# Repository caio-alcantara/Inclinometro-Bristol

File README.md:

# Inclinometro-Bristol
Projeto de um inclinômetro desenvolvido para a Bristol. Um dispositivo capaz de medir a angulação de perfuratrizes e enviar esse dado via bluetooth para o operador da máquina.

Desenvolvedor: <a href="https://www.linkedin.com/in/caio-alcantara-santos/">Caio de Alcantara Santos</a>

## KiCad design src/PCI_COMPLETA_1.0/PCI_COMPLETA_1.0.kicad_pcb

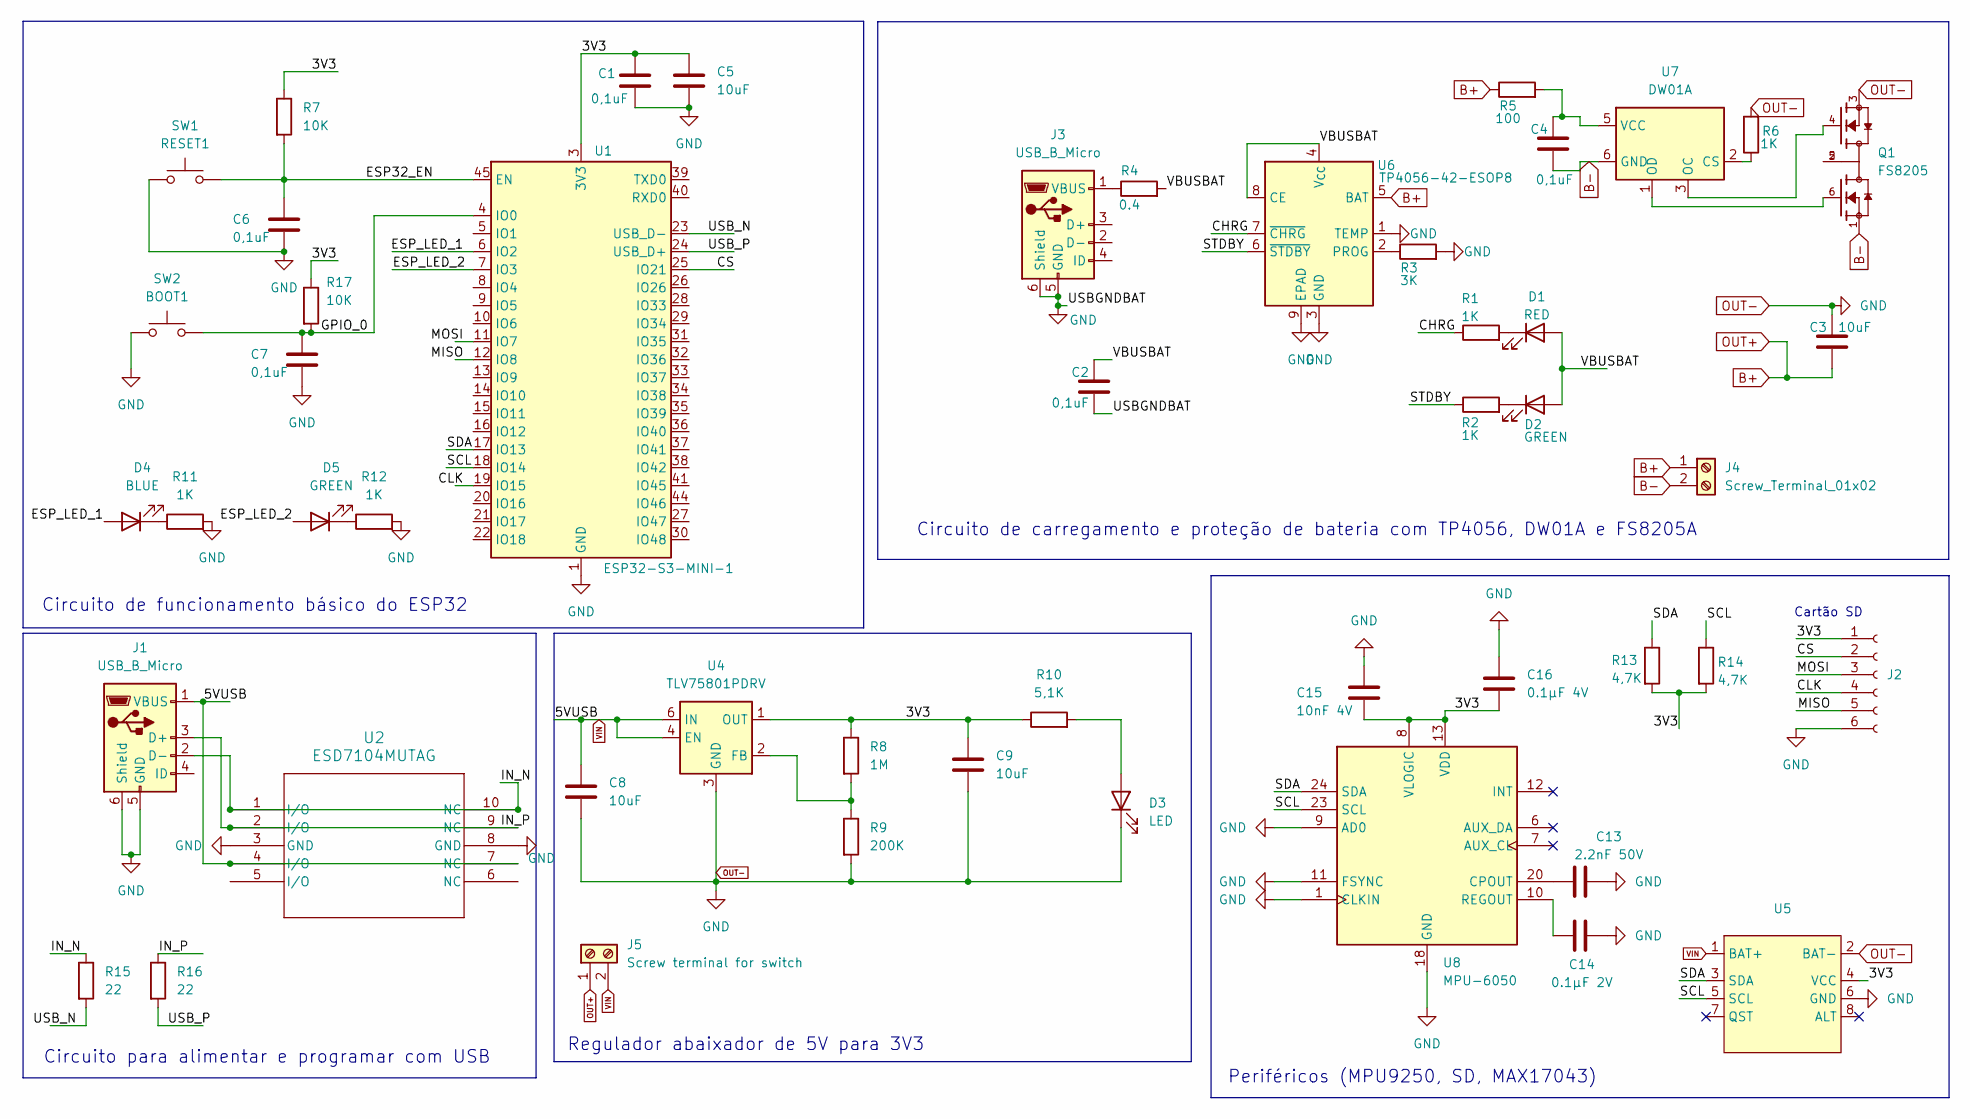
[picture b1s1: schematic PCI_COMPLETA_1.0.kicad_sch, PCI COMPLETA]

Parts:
C1, C2, C4, C6, C7: 0,1uF; C_0603_1608Metric
C3, C5, C8, C9: 10uF; C_0603_1608Metric
C13: 2.2nF 50V; C_0603_1608Metric
C14: 0.1µF 2V; C_0603_1608Metric
C15: 10nF 4V; C_0603_1608Metric
C16: 0.1µF 4V; C_0603_1608Metric
D1: RED; LED_0603_1608Metric
D2, D5: GREEN; LED_0603_1608Metric
D3: LED; LED_0603_1608Metric
D4: BLUE; LED_0603_1608Metric
J1, J3: USB_B_Micro; USB_Micro-B_Molex-105017-0001
J2: Conn_01x06_Socket; PinSocket_1x06_P2.54mm_Vertical
J4: Screw_Terminal_01x02; mors_2p
J5: Screw terminal for switch; mors_2p
Q1: FS8205; SOT95P280X145-6N; PARTREV 1.9
R1, R2, R6, R11, R12: 1K; R_0603_1608Metric
R3: 3K; R_0603_1608Metric
R4: 0.4; R_0603_1608Metric
R5: 100; R_0603_1608Metric
R7, R17: 10K; R_0603_1608Metric
R8: 1M; R_0603_1608Metric
R9: 200K; R_0603_1608Metric
R10: 5,1K; R_0603_1608Metric
R13, R14: 4,7K; R_0603_1608Metric
R15, R16: 22; R_0402_1005Metric
SW1: RESET1; SW_Push_1P1T_NO_CK_KSC6xxJ
SW2: BOOT1; SW_Push_1P1T_NO_CK_KSC6xxJ
U1: ESP32-S3-MINI-1; XCVR_ESP32-S3-MINI-1-N8
U2: ESD7104MUTAG; UDFN10_ONS
U4: TLV75801PDRV; WSON-6-1EP_2x2mm_P0.65mm_EP1x1.6mm
U5: MAX
U6: TP4056-42-ESOP8; SOIC-8-1EP_3.9x4.9mm_P1.27mm_EP2.41x3.3mm_ThermalVias
U7: DW01A; SOT-23-6
U8: MPU-6050; InvenSense_QFN-24_4x4mm_P0.5mm

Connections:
/3V3: C1.1, C5.1, C9.1, C15.2, C16.2, J2.1, R7.1, R8.1, R10.1, R13.2, R14.2, R17.1, U1.3 (3V3), U4.1 (OUT), U5.4 (VCC), U8.8 (VLOGIC), U8.13 (VDD)
/CHRG: R1.1, U6.7 (~CHRG)
/CLK: J2.4, U1.19 (IO15)
/CS: J2.2, U1.25 (IO21)
/ESP32_EN: C6.1, R7.2, SW1.2, U1.45 (EN)
/ESP_LED_1: D4.2 (A), U1.6 (IO2)
/ESP_LED_2: D5.2 (A), U1.7 (IO3)
/GPIO_0: C7.1, R17.2, SW2.2, U1.4 (IO0)
/IN_N: J1.2 (D-), R15.1, U2.1 (I/O), U2.10 (NC)
/IN_P: J1.3 (D+), R16.1, U2.2 (I/O), U2.9 (NC)
/MISO: J2.5, U1.12 (IO8)
/MOSI: J2.3, U1.11 (IO7)
/SCL: R14.1, U1.18 (IO14), U5.5 (SCL), U8.23 (SCL)
/SDA: R13.1, U1.17 (IO13), U5.3 (SDA), U8.24 (SDA)
/STDBY: R2.1, U6.6 (~STDBY)
/USB_N: R15.2, U1.23 (USB_D-)
/USB_P: R16.2, U1.24 (USB_D+)
/VBUSBAT: C2.1, D1.2 (A), D2.2 (A), R4.2, U6.4 (V_{CC}), U6.8 (CE)
B+: C3.2, J4.1, J5.1, R5.1, U6.5 (BAT)
B-: C4.2, J4.2, Q1.1, U7.6 (GND)
unnamed: D1.1 (K), R1.2
unnamed: D2.1 (K), R2.2
unnamed: D3.2 (A), R10.2
unnamed: D4.1 (K), R11.1
unnamed: D5.1 (K), R12.1
unnamed: J3.1 (VBUS), R4.1
unnamed: Q1.2, Q1.5
unnamed: R8.2, R9.1, U4.2 (FB)
unnamed: R3.1, U6.2 (PROG)
unnamed: R6.1, U7.2 (CS)
unnamed: Q1.4, U7.3 (OC)
unnamed: Q1.6, U7.1 (OD)
unnamed: C4.1, R5.2, U7.5 (VCC)
unnamed: C13.2, U8.20 (CPOUT)
unnamed: C14.2, U8.10 (REGOUT)
OUT-: C1.2, C2.2, C3.1, C5.2, C6.2, C7.2, C8.2, C9.2, C13.1, C14.1, C15.1, C16.1, D3.1 (K), J1.5 (GND), J1.6 (Shield), J2.6, J3.5 (GND), J3.6 (Shield), Q1.3, R3.2, R6.2, R9.2, R11.2, R12.2, SW1.1, SW2.1, U1.1 (GND), U1.2 (GND), U1.42 (GND), U1.43 (GND), U1.46 (GND), U1.47 (GND), U1.48 (GND), U1.49 (GND), U1.50 (GND), U1.51 (GND), U1.52 (GND), U1.53 (GND), U1.54 (GND), U1.55 (GND), U1.56 (GND), U1.57 (GND), U1.58 (GND), U1.59 (GND), U1.60 (GND), U1.61 (GND), U1.62 (GND), U1.63 (GND), U1.64 (GND), U1.65 (GND), U2.3 (GND), U2.8 (GND), U4.3 (GND), U4.7 (GND), U5.2 (BAT-), U5.6 (GND), U6.1 (TEMP), U6.3 (GND), U6.9 (EPAD), U8.1 (CLKIN), U8.9 (AD0), U8.11 (FSYNC), U8.18 (GND)
VIN: C8.1, J1.1 (VBUS), J5.2, U2.4 (I/O), U2.7 (NC), U4.4 (EN), U4.6 (IN), U5.1 (BAT+)

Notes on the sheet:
Circuito de funcionamento básico do ESP32
Regulador abaixador de 5V para 3V3
Circuito para alimentar e programar com USB
Cartão SD
Periféricos (MPU9250, SD, MAX17043)
Circuito de carregamento e proteção de bateria com TP4056, DW01A e FS8205A

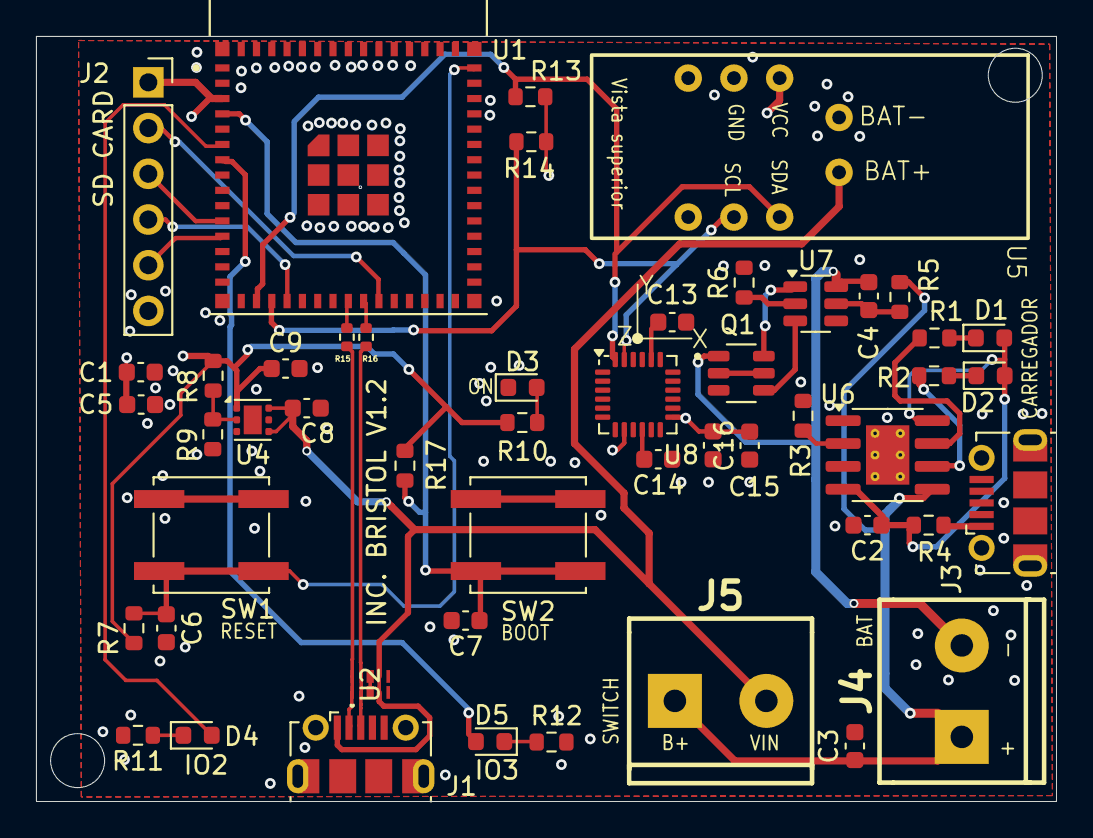
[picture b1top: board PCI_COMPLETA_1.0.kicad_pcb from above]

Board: 4 copper layers, 56.7 x 42.5 mm, 50 parts (0 on the bottom side), 37 nets.

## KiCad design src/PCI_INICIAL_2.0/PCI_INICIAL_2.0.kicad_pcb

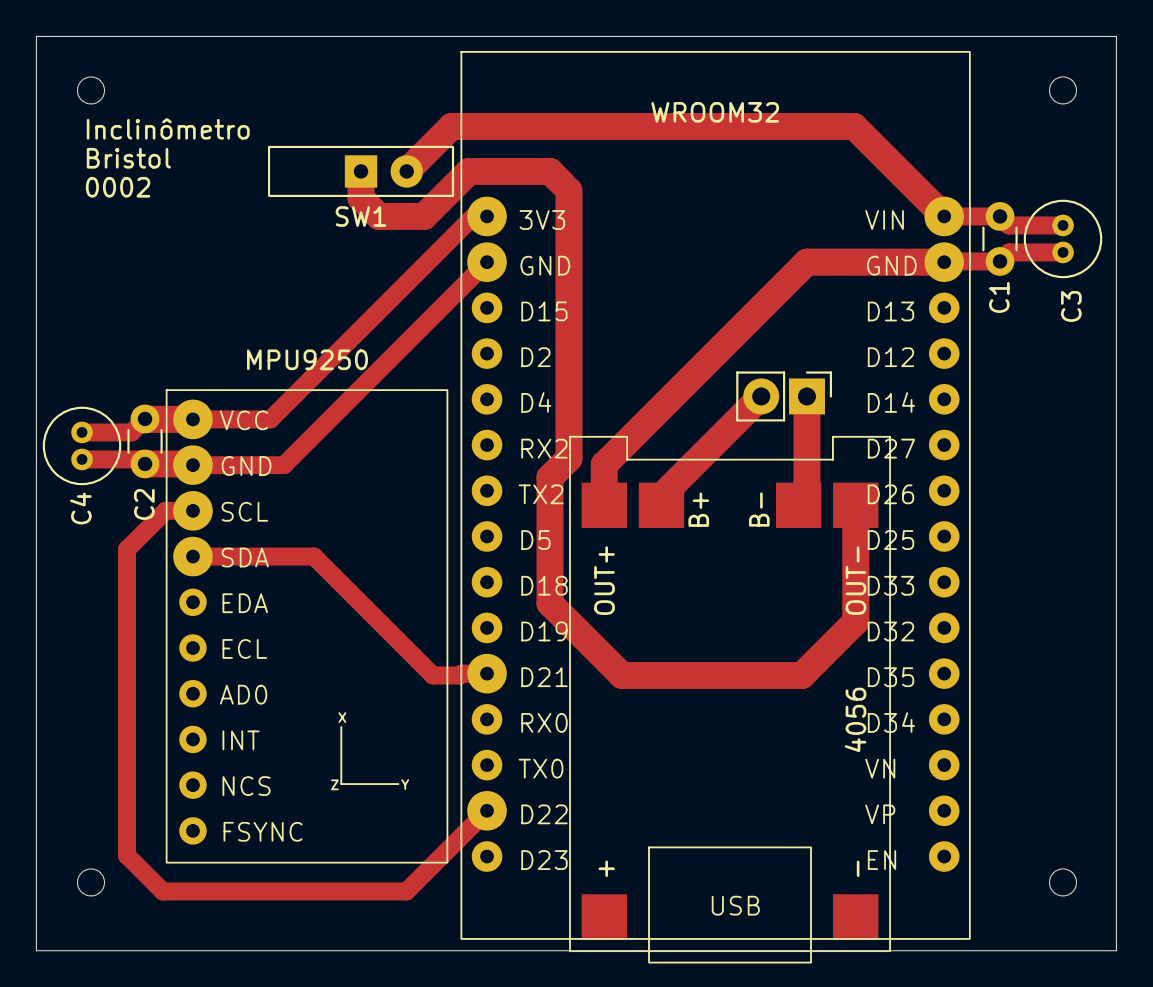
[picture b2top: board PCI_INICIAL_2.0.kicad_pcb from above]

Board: 2 copper layers, 60.0 x 50.8 mm, 9 parts (0 on the bottom side), 8 nets.

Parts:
C1, C2: 104 100nF; C_Disc_D3.0mm_W1.6mm_P2.50mm
C3, C4: 10uF 16V; C_Radial_D4.0mm_H5.0mm_P1.50mm
J1: 2 male pin header; PinHeader_1x02_P2.54mm_Vertical
SW1: Switch; SW_Slide-03_Wuerth-WS-SLTV_10x2.5x6.4_P2.54mm
U1: ESP32; ESP32-Wroom-32-Module
U2: MPU9250 Module; MPU9250_Module
U3: TP4056

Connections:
3V3: C2.1, C4.1, U1.1 (3V3), U2.1 (VCC)
B+: J1.2, U3.2 (B+)
B-: J1.1, U3.3 (B-)
GND: C1.2, C2.2, C3.2, C4.2, U1.2 (GND), U1.17 (GND), U2.2 (GND), U3.1 (OUT-)
OUT+: SW1.1, U3.4 (OUT+)
SCL: U1.14 (D22), U2.3 (SCL)
SDA: U1.11 (D21), U2.4 (SDA)
VIN: C1.1, C3.E, SW1.2, U1.16 (VIN)

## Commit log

2025-01-22 docs: adiciona autor do projeto ao readme
2025-01-22 chore: adiciona estrutura de pastas inicial do projeto
2025-01-22 docs: adiciona introducao ao documento, entregaveis e persona
2025-01-23 docs: adiciona secao de storyboard na documentacao
2025-01-25 docs: adiciona requisitos funcionais e nao-funcionais
2025-01-26 docs: adiciona arquitetura simplificada da solucao & desenvolvimento continuo do projeto + introducao a simulacao
2025-01-26 feat: adiciona codigo utilizado em simulacao wokwi
2025-01-26 docs: adiciona casos de teste da simulacao
2025-01-31 docs: adiciona user stories da persona
2025-02-02 docs: adiciona link e imagem da simulação no wokwi
2025-02-05 feat: adiciona versao inicial de código modularizado do dispositivo fisico
2025-02-06 feat: adiciona envio de dados via BLE BLE: Bluetooth Low Energy
2025-02-10 feat: adiciona envio de angulo em demais eixos via bluetooth
2025-02-17 feat: adiciona arquivos de placa de circuito impressa
2025-02-17 docs: adiciona documentacao de primeiro mes
2025-02-21 feat: adiciona arquivos 2.0 de PCI
2025-02-21 docs: adiciona documentacao final de primeiro mes
2025-03-20 feat: adiciona placa 2.0 e novo firmware
2025-03-21 feat: corrige erros do leitor de bateria e adiciona led ble
2025-03-21 fix: corrige declaracao de string
2025-03-23 fix: corrige erros de envio de dados e nome do dispositivo
2025-03-23 feat: adiciona armazenamento de dados no cartão sd
2025-03-24 docs: adiciona documentação de final de 2o mes
2025-03-29 feat: adiciona libs kicad
2025-04-22 feat: adiciona modificacoes para esp32 s3
2025-05-03 feat/docs: adiciona documentacao 3o mes e PCI Industrial
2025-05-20 feat: adiciona OTA inicial
2025-06-15 fix: corrige envio de valores de angulo
